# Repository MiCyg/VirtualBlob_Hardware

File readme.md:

# Virtual Blob Hardware

[← Back to main repository](https://github.com/MiCyg/VirtualBlob.git)

---

The device consists of three PCBs:
- `MainBoard` – microcontroller and peripheral interfaces
- `PowerBoard` – USB connector and battery charging circuit
- `LedBoard` – LED matrix driven by the MAX7219

Components on the boards:
- RP2040 microcontroller with SWD programming interface
- Accelerometer LIS3DH
- Capacitive touch sensor AT42QT1011
- Light sensor (LDR with resistor divider)
- Li-Po battery (LP852040)
- Battery charger MCP73811T

## Description

The `MainBoard` and `PowerBoard` are connected using a custom-designed `EdgeConn` board-to-board connector, allowing a 90° connection between the two.
Due to the small overall size and the position of the USB connector, I decided to use a ready-made LED matrix module. This approach saves valuable PCB space on the `MainBoard`, which is limited by the placement of the edge connector.

The device is designed to operate continuously from a Li-Po battery. Therefore, proper power management in sleep mode is crucial. To reduce power consumption, a high-side P-MOSFET switch is used to disconnect the accelerometer and light sensors when the system enters sleep mode. The capacitive touch sensor remains powered at all times, as it is responsible for waking up the device.

## Assembled Boards

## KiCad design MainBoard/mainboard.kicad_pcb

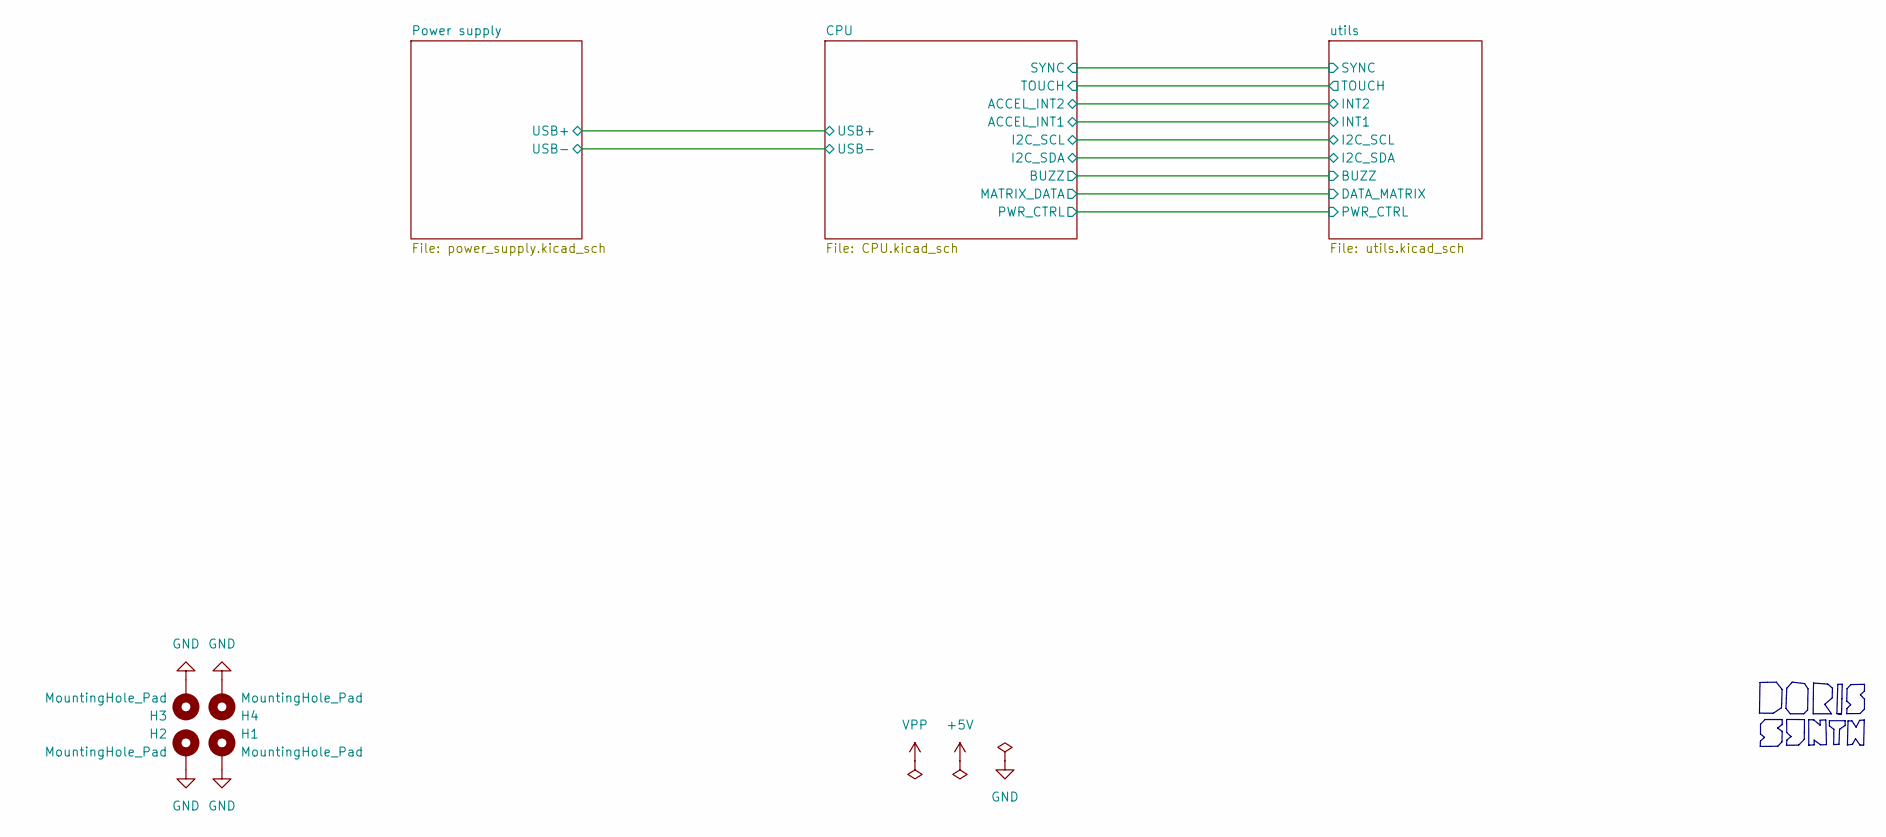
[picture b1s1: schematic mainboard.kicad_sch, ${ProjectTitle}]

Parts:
H1, H2, H3, H4: MountingHole_Pad; MountingHole_2.5mm

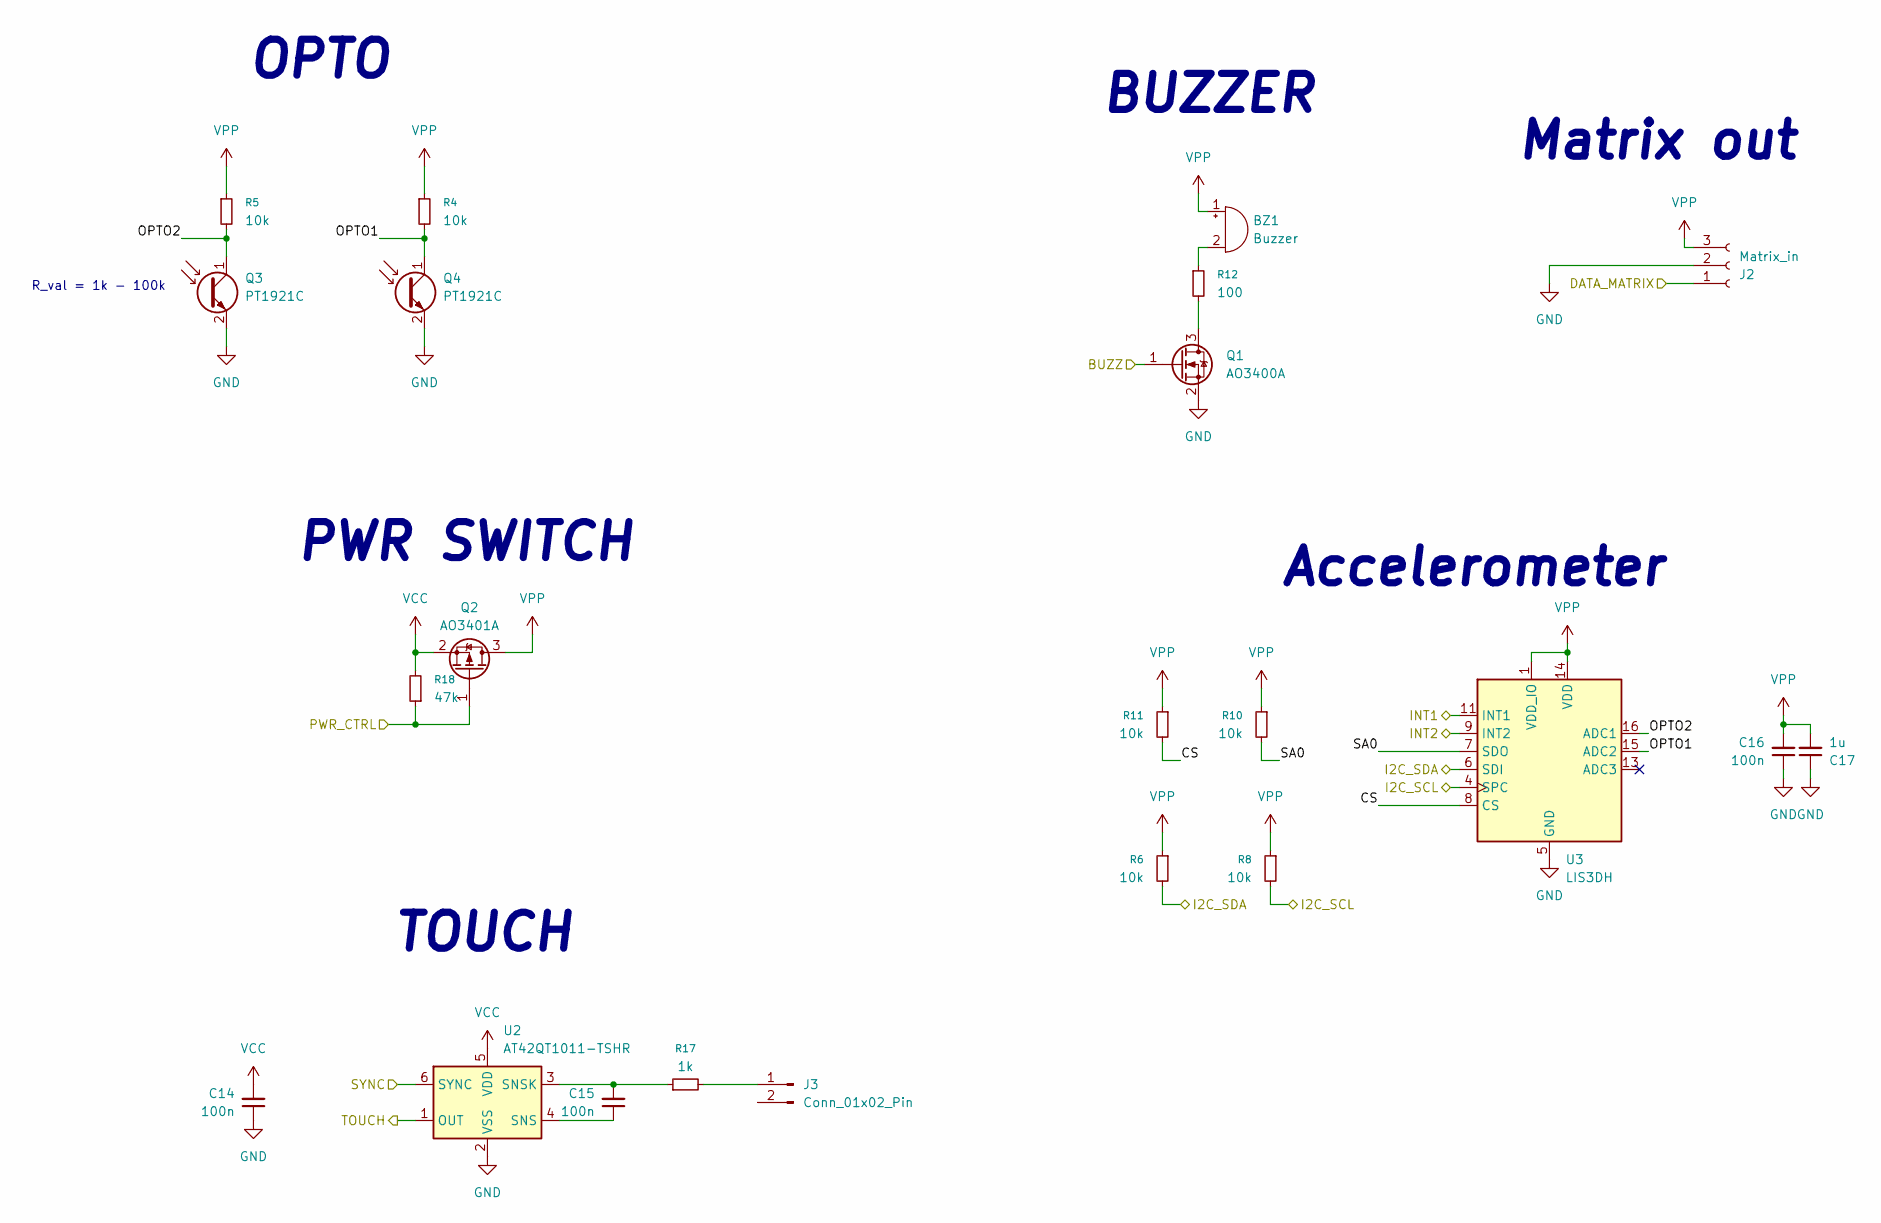
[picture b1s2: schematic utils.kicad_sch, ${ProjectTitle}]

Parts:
BZ1: Buzzer; Buzzer_SMD_5020
C14, C15, C16: 100n; C_0603_1608Metric_Pad1.08x0.95mm_HandSolder
C17: 1u; C_0603_1608Metric_Pad1.08x0.95mm_HandSolder
J2: Matrix_in; JST_PH_B3B-PH-K_1x03_P2.00mm_Vertical
J3: Conn_01x02_Pin; FW-UU_04_08_15
Q1: AO3400A; SOT-23
Q2: AO3401A; SOT-23
Q3, Q4: PT1921C; D_0603_1608Metric_Pad1.05x0.95mm_HandSolder
R4, R5, R6, R8, R10, R11: 10k; R_0603_1608Metric_Pad0.98x0.95mm_HandSolder
R12: 100; R_0603_1608Metric_Pad0.98x0.95mm_HandSolder
R17: 1k; R_0603_1608Metric_Pad0.98x0.95mm_HandSolder
R18: 47k; R_0603_1608Metric_Pad0.98x0.95mm_HandSolder
U2: AT42QT1011-TSHR; SOT-23-6
U3: LIS3DH; LGA-16_3x3mm_P0.5mm_LayoutBorder3x5y

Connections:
/CPU/ACCEL_INT1: U3.11 (INT1); also elsewhere on the board
/CPU/ACCEL_INT2: U3.9 (INT2); also elsewhere on the board
/CPU/BUZZ: Q1.1 (G); also elsewhere on the board
/CPU/I2C_SCL: R8.2, U3.4 (SPC); also elsewhere on the board
/CPU/I2C_SDA: R6.2, U3.6 (SDI); also elsewhere on the board
/CPU/MATRIX_DATA: J2.1; also elsewhere on the board
/CPU/PWR_CTRL: Q2.1 (G), R18.1; also elsewhere on the board
/CPU/SYNC: U2.6 (SYNC); also elsewhere on the board
/CPU/TOUCH: U2.1 (OUT); also elsewhere on the board
/utils/CS: R11.2, U3.8 (CS)
/utils/OPTO1: Q4.1 (C), R4.2, U3.15 (ADC2)
/utils/OPTO2: Q3.1 (C), R5.2, U3.16 (ADC1)
/utils/SA0: R10.2, U3.7 (SDO)
GND: C14.1, C16.1, C17.1, J2.2, Q1.2 (S), Q3.2 (E), Q4.2 (E), U2.2 (VSS), U3.5 (GND), U3.10 (GND), U3.12 (GND); also elsewhere on the board
unnamed: BZ1.2 (-), R12.1
unnamed: J3.1, R17.2
unnamed: Q1.3 (D), R12.2
unnamed: C15.1, U2.4 (SNS)
unnamed: C15.2, R17.1, U2.3 (SNSK)
VCC: C14.2, Q2.2 (S), R18.2, U2.5 (VDD); also elsewhere on the board
VPP: BZ1.1 (+), C16.2, C17.2, J2.3, Q2.3 (D), R4.1, R5.1, R6.1, R8.1, R10.1, R11.1, U3.1 (VDD_IO), U3.14 (VDD)

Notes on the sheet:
OPTO
R_val = 1k - 100k
Matrix out
PWR SWITCH
BUZZER
TOUCH
Accelerometer

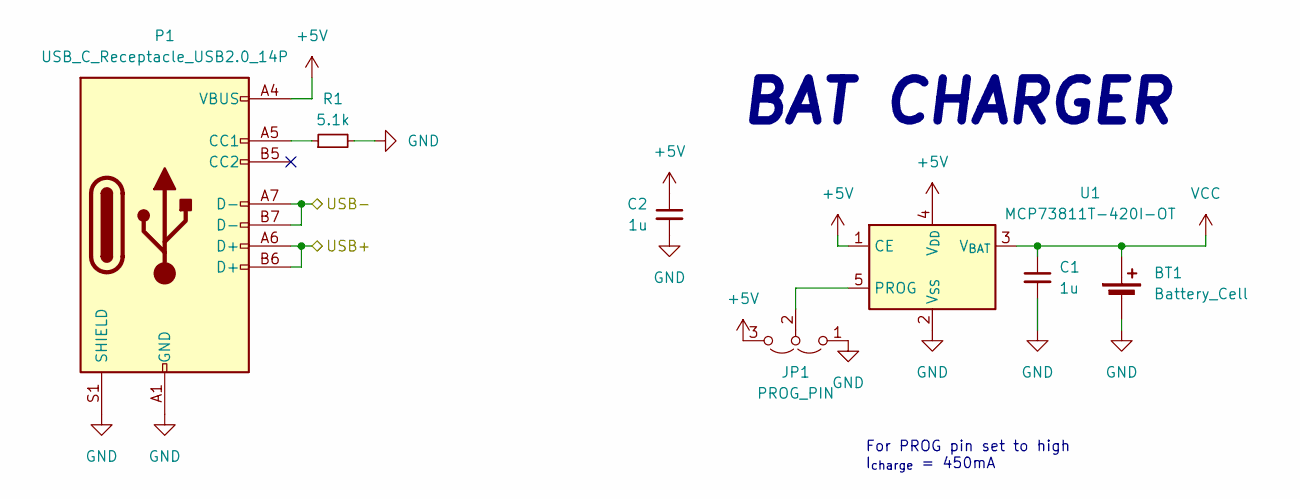
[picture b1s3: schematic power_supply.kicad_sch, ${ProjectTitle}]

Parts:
BT1: Battery_Cell; Molex_PicoBlade_53047-0210_1x02_P1.25mm_Vertical
C1, C2: 1u; C_0603_1608Metric_Pad1.08x0.95mm_HandSolder
JP1: PROG_PIN; SolderJumper-3_P1.3mm_Open_RoundedPad1.0x1.5mm
P1: USB_C_Receptacle_USB2.0_14P; USB_C_Receptacle_G-Switch_GT-USB-7010ASV
R1: 5.1k; R_0603_1608Metric_Pad0.98x0.95mm_HandSolder
U1: MCP73811T-420I-OT; SOT-23-5

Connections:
+5V: C2.1, JP1.3 (B), P1.A4 (VBUS), P1.A9 (VBUS), P1.B4 (VBUS), P1.B9 (VBUS), U1.1 (CE), U1.4 (V_{DD})
/CPU/USB+: P1.A6 (D+), P1.B6 (D+); also elsewhere on the board
/CPU/USB-: P1.A7 (D-), P1.B7 (D-); also elsewhere on the board
GND: BT1.2 (-), C1.2, C2.2, JP1.1 (A), P1.A1 (GND), P1.A12 (GND), P1.B1 (GND), P1.B12 (GND), P1.S1 (SHIELD), R1.2, U1.2 (V_{SS}); also elsewhere on the board
unnamed: JP1.2 (C), U1.5 (PROG)
unnamed: P1.A5 (CC1), R1.1
VCC: BT1.1 (+), C1.1, U1.3 (V_{BAT}); also elsewhere on the board

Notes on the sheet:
BAT CHARGER
For PROG pin set to high I_{charge} = 450mA

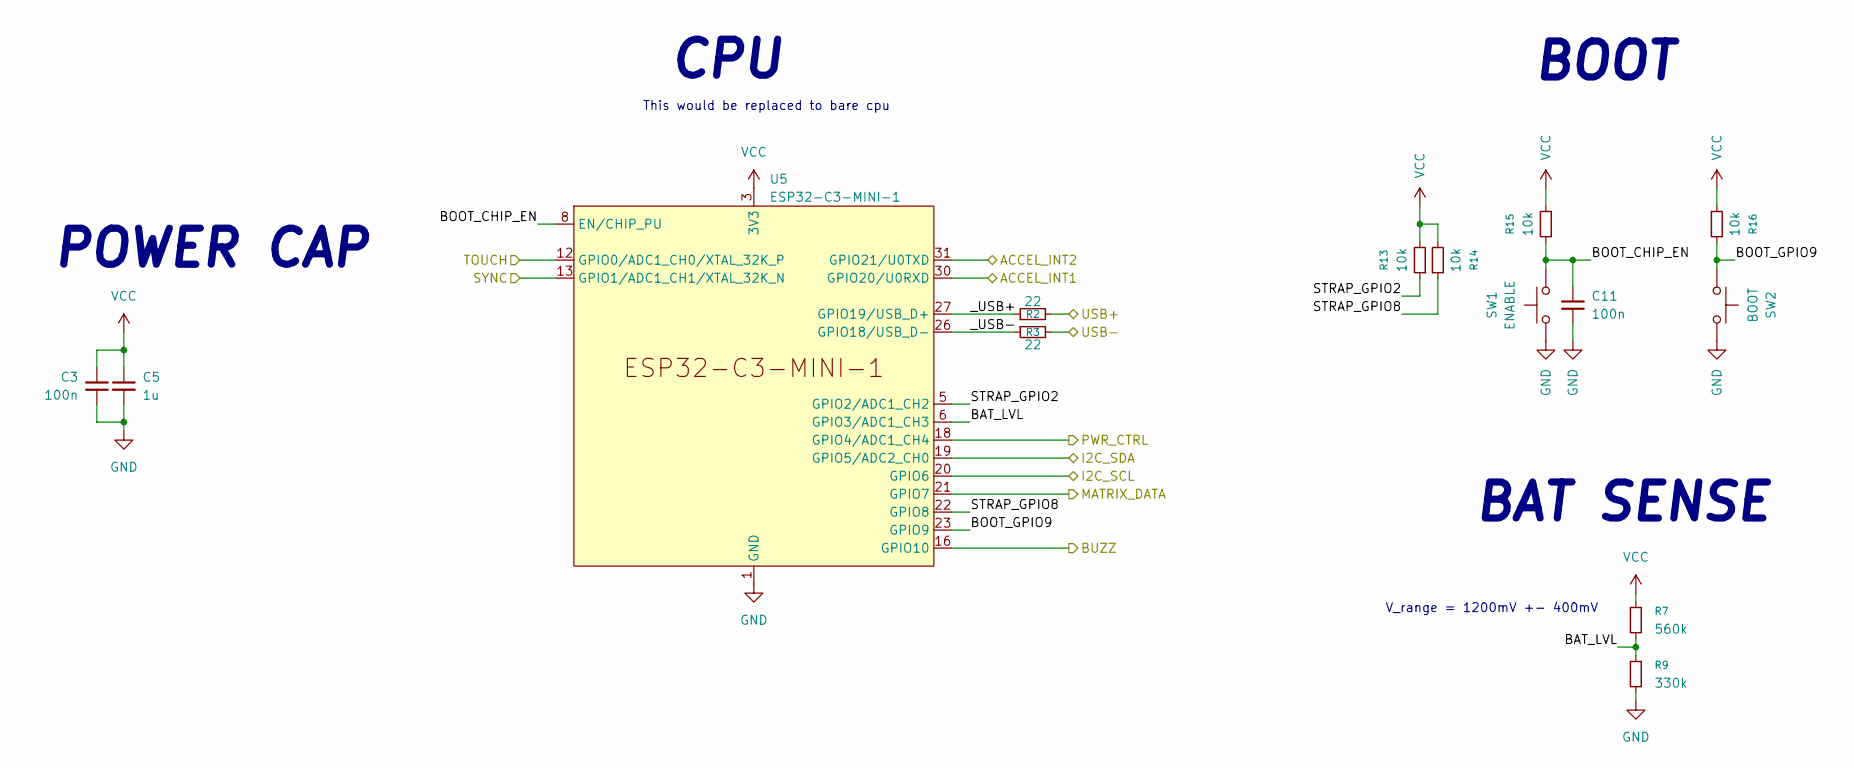
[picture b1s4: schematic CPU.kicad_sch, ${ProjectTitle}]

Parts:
C3, C11: 100n; C_0603_1608Metric_Pad1.08x0.95mm_HandSolder
C5: 1u; C_0603_1608Metric_Pad1.08x0.95mm_HandSolder
R2, R3: 22; R_0603_1608Metric_Pad0.98x0.95mm_HandSolder
R7: 560k; R_0603_1608Metric_Pad0.98x0.95mm_HandSolder
R9: 330k; R_0603_1608Metric_Pad0.98x0.95mm_HandSolder
R13, R14, R15, R16: 10k; R_0603_1608Metric_Pad0.98x0.95mm_HandSolder
SW1: ENABLE; SW_SPST_CK_RS282G05A3
SW2: BOOT; SW_SPST_CK_RS282G05A3
U5: ESP32-C3-MINI-1

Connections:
/CPU/ACCEL_INT1: U5.30 (GPIO20/U0RXD); also elsewhere on the board
/CPU/ACCEL_INT2: U5.31 (GPIO21/U0TXD); also elsewhere on the board
/CPU/BAT_LVL: R7.2, R9.1, U5.6 (GPIO3/ADC1_CH3)
/CPU/BOOT_CHIP_EN: C11.2, R15.2, SW1.2, U5.8 (EN/CHIP_PU)
/CPU/BOOT_GPIO9: R16.2, SW2.2, U5.23 (GPIO9)
/CPU/BUZZ: U5.16 (GPIO10); also elsewhere on the board
/CPU/I2C_SCL: U5.20 (GPIO6); also elsewhere on the board
/CPU/I2C_SDA: U5.19 (GPIO5/ADC2_CH0); also elsewhere on the board
/CPU/MATRIX_DATA: U5.21 (GPIO7); also elsewhere on the board
/CPU/PWR_CTRL: U5.18 (GPIO4/ADC1_CH4); also elsewhere on the board
/CPU/STRAP_GPIO2: R13.1, U5.5 (GPIO2/ADC1_CH2)
/CPU/STRAP_GPIO8: R14.1, U5.22 (GPIO8)
/CPU/SYNC: U5.13 (GPIO1/ADC1_CH1/XTAL_32K_N); also elsewhere on the board
/CPU/TOUCH: U5.12 (GPIO0/ADC1_CH0/XTAL_32K_P); also elsewhere on the board
/CPU/USB+: R2.2; also elsewhere on the board
/CPU/USB-: R3.2; also elsewhere on the board
/CPU/_USB+: R2.1, U5.27 (GPIO19/USB_D+)
/CPU/_USB-: R3.1, U5.26 (GPIO18/USB_D-)
GND: C3.1, C5.2, C11.1, R9.2, SW1.1, SW2.1, U5.1 (GND), U5.2 (GND), U5.11 (GND), U5.14 (GND), U5.36 (GND), U5.37 (GND), U5.38 (GND), U5.39 (GND), U5.40 (GND), U5.41 (GND), U5.42 (GND), U5.43 (GND), U5.44 (GND), U5.45 (GND), U5.46 (GND), U5.47 (GND), U5.48 (GND), U5.49 (GND), U5.50 (GND), U5.51 (GND), U5.52 (GND), U5.53 (GND); also elsewhere on the board
VCC: C3.2, C5.1, R7.1, R13.2, R14.2, R15.1, R16.1, U5.3 (3V3); also elsewhere on the board

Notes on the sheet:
CPU
BOOT
This would be replaced to bare cpu
BAT SENSE
POWER CAP
V_range = 1200mV +- 400mV

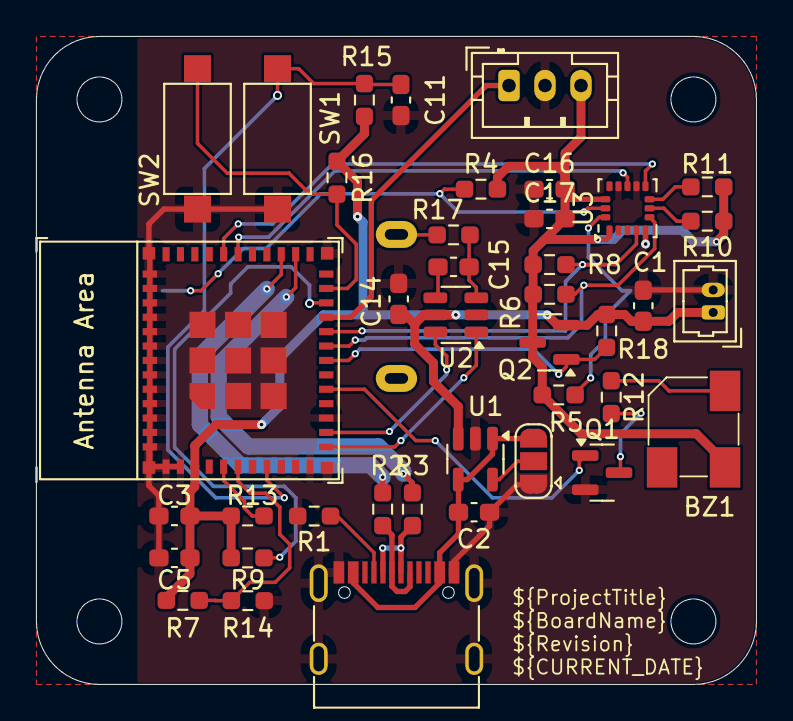
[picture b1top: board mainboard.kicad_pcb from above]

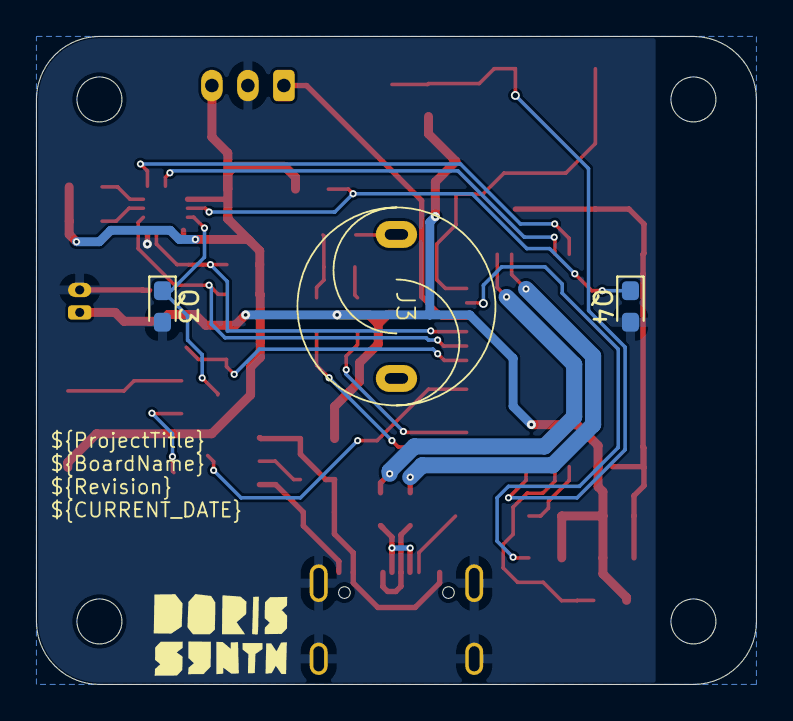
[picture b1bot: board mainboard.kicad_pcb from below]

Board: 2 copper layers, 40.0 x 36.0 mm, 47 parts (3 on the bottom side), 33 nets.

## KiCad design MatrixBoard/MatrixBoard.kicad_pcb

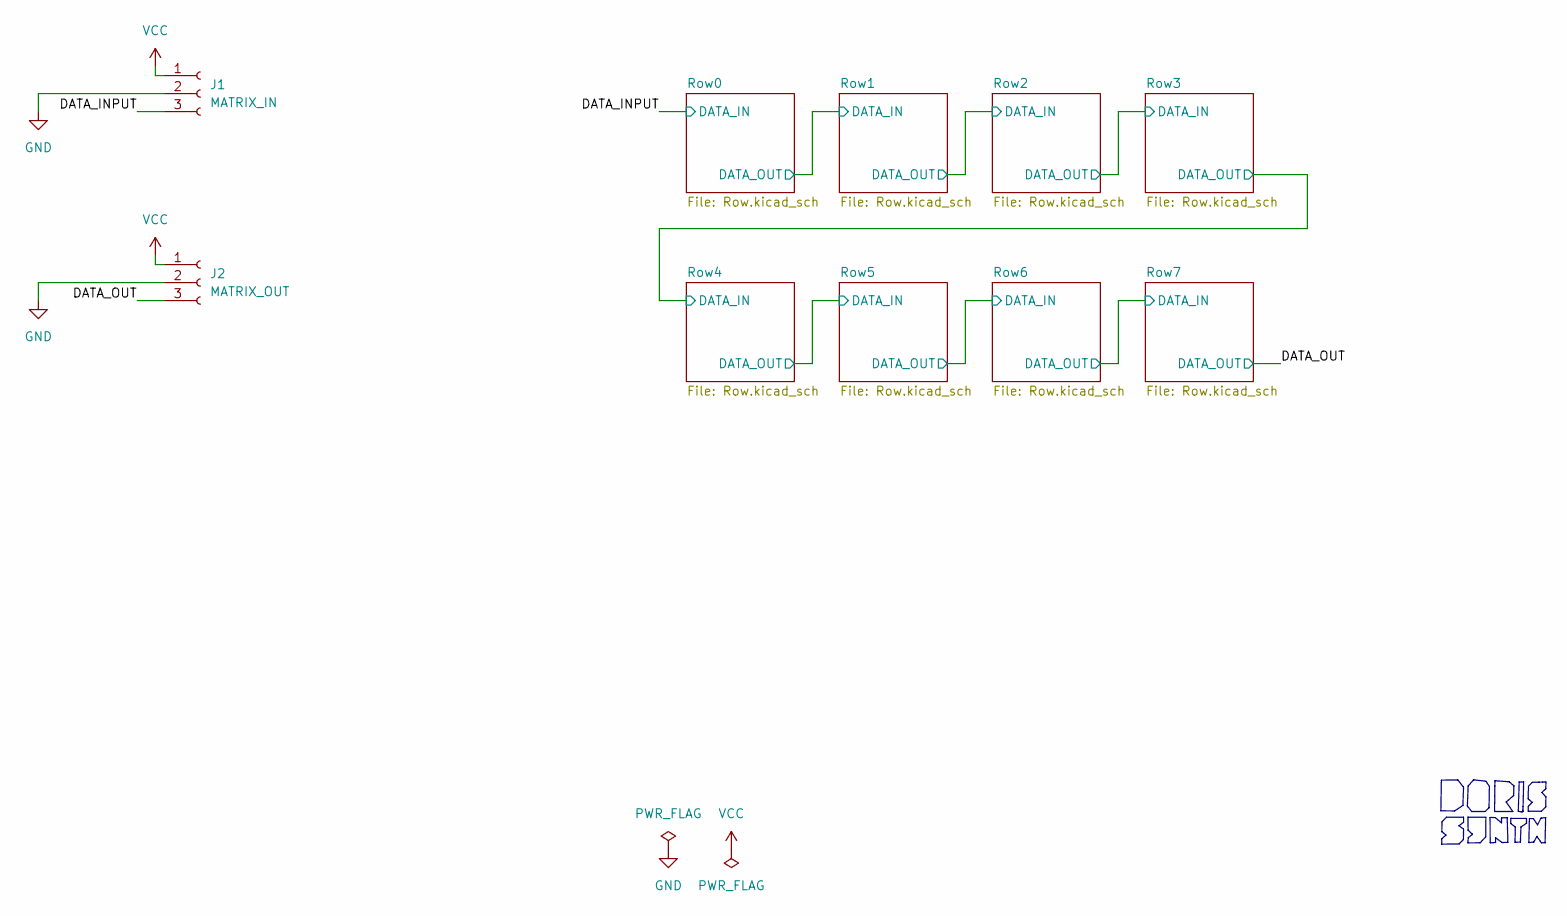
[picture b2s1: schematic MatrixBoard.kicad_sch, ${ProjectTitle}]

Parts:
J1: MATRIX_IN; PinHeader_1x03_P2.54mm_Vertical
J2: MATRIX_OUT; PinHeader_1x03_P2.54mm_Vertical

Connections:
/DATA_INPUT: J1.3; also elsewhere on the board
/DATA_OUT: J2.3; also elsewhere on the board
GND: J1.2, J2.2; also elsewhere on the board
VCC: J1.1, J2.1; also elsewhere on the board

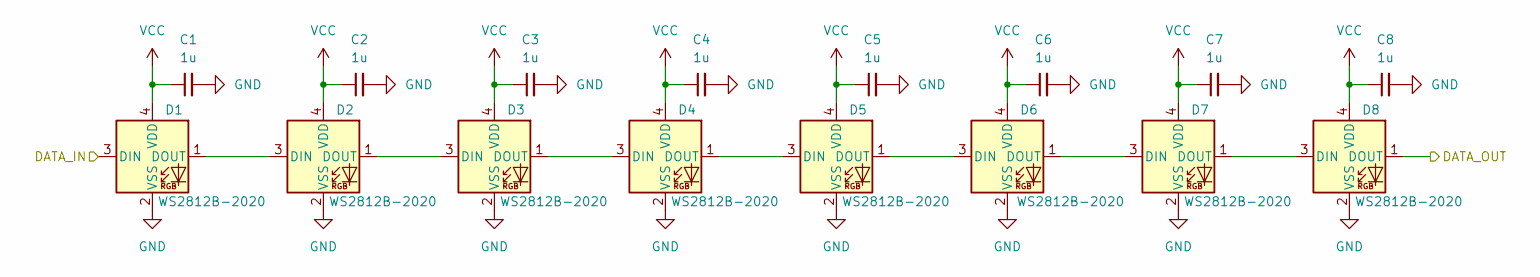
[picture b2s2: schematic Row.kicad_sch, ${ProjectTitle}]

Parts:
C1, C2, C3, C4, C5, C6, C7, C8: 1u; C_0603_1608Metric_Pad1.08x0.95mm_HandSolder
D1, D2, D3, D4, D5, D6, D7, D8: WS2812B-2020; LED_WS2812B-2020_PLCC4_2.0x2.0mm

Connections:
/DATA_INPUT: D1.3 (DIN); also elsewhere on the board
/Row0/DATA_OUT: D8.1 (DOUT); also elsewhere on the board
GND: C1.2, C2.2, C3.2, C4.2, C5.2, C6.2, C7.2, C8.2, D1.2 (VSS), D2.2 (VSS), D3.2 (VSS), D4.2 (VSS), D5.2 (VSS), D6.2 (VSS), D7.2 (VSS), D8.2 (VSS); also elsewhere on the board
unnamed: D1.1 (DOUT), D2.3 (DIN)
unnamed: D2.1 (DOUT), D3.3 (DIN)
unnamed: D3.1 (DOUT), D4.3 (DIN)
unnamed: D4.1 (DOUT), D5.3 (DIN)
unnamed: D5.1 (DOUT), D6.3 (DIN)
unnamed: D6.1 (DOUT), D7.3 (DIN)
unnamed: D7.1 (DOUT), D8.3 (DIN)
VCC: C1.1, C2.1, C3.1, C4.1, C5.1, C6.1, C7.1, C8.1, D1.4 (VDD), D2.4 (VDD), D3.4 (VDD), D4.4 (VDD), D5.4 (VDD), D6.4 (VDD), D7.4 (VDD), D8.4 (VDD); also elsewhere on the board

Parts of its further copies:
C9, C10, C11, C12, C13, C14, C15, C16, C17, C18, C19, C20, C21, C22, C23, C24, C25, C26, C27, C28, C29, C30, C31, C32, C33, C34, C35, C36, C37, C38, C39, C40, C41, C42, C43, C44, C45, C46, C47, C48, C49, C50, C51, C52, C53, C54, C55, C56, C57, C58, C59, C60, C61, C62, C63, C64: 1u; C_0603_1608Metric_Pad1.08x0.95mm_HandSolder
D9, D10, D11, D12, D13, D14, D15, D16, D17, D18, D19, D20, D21, D22, D23, D24, D25, D26, D27, D28, D29, D30, D31, D32, D33, D34, D35, D36, D37, D38, D39, D40, D41, D42, D43, D44, D45, D46, D47, D48, D49, D50, D51, D52, D53, D54, D55, D56, D57, D58, D59, D60, D61, D62, D63, D64: WS2812B-2020; LED_WS2812B-2020_PLCC4_2.0x2.0mm

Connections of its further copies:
/DATA_OUT: D64.1 (DOUT); also elsewhere on the board
/Row0/DATA_OUT: D9.3 (DIN); also elsewhere on the board
/Row1/DATA_OUT: D16.1 (DOUT), D17.3 (DIN)
/Row2/DATA_OUT: D24.1 (DOUT), D25.3 (DIN)
/Row3/DATA_OUT: D32.1 (DOUT), D33.3 (DIN)
/Row4/DATA_OUT: D40.1 (DOUT), D41.3 (DIN)
/Row5/DATA_OUT: D48.1 (DOUT), D49.3 (DIN)
/Row6/DATA_OUT: D56.1 (DOUT), D57.3 (DIN)
GND: C9.2, C10.2, C11.2, C12.2, C13.2, C14.2, C15.2, C16.2, C17.2, C18.2, C19.2, C20.2, C21.2, C22.2, C23.2, C24.2, C25.2, C26.2, C27.2, C28.2, C29.2, C30.2, C31.2, C32.2, C33.2, C34.2, C35.2, C36.2, C37.2, C38.2, C39.2, C40.2, C41.2, C42.2, C43.2, C44.2, C45.2, C46.2, C47.2, C48.2, C49.2, C50.2, C51.2, C52.2, C53.2, C54.2, C55.2, C56.2, C57.2, C58.2, C59.2, C60.2, C61.2, C62.2, C63.2, C64.2, D9.2 (VSS), D10.2 (VSS), D11.2 (VSS), D12.2 (VSS), D13.2 (VSS), D14.2 (VSS), D15.2 (VSS), D16.2 (VSS), D17.2 (VSS), D18.2 (VSS), D19.2 (VSS), D20.2 (VSS), D21.2 (VSS), D22.2 (VSS), D23.2 (VSS), D24.2 (VSS), D25.2 (VSS), D26.2 (VSS), D27.2 (VSS), D28.2 (VSS), D29.2 (VSS), D30.2 (VSS), D31.2 (VSS), D32.2 (VSS), D33.2 (VSS), D34.2 (VSS), D35.2 (VSS), D36.2 (VSS), D37.2 (VSS), D38.2 (VSS), D39.2 (VSS), D40.2 (VSS), D41.2 (VSS), D42.2 (VSS), D43.2 (VSS), D44.2 (VSS), D45.2 (VSS), D46.2 (VSS), D47.2 (VSS), D48.2 (VSS), D49.2 (VSS), D50.2 (VSS), D51.2 (VSS), D52.2 (VSS), D53.2 (VSS), D54.2 (VSS), D55.2 (VSS), D56.2 (VSS), D57.2 (VSS), D58.2 (VSS), D59.2 (VSS), D60.2 (VSS), D61.2 (VSS), D62.2 (VSS), D63.2 (VSS), D64.2 (VSS); also elsewhere on the board
unnamed: D9.1 (DOUT), D10.3 (DIN)
unnamed: D10.1 (DOUT), D11.3 (DIN)
unnamed: D11.1 (DOUT), D12.3 (DIN)
unnamed: D12.1 (DOUT), D13.3 (DIN)
unnamed: D13.1 (DOUT), D14.3 (DIN)
unnamed: D14.1 (DOUT), D15.3 (DIN)
unnamed: D15.1 (DOUT), D16.3 (DIN)
unnamed: D17.1 (DOUT), D18.3 (DIN)
unnamed: D18.1 (DOUT), D19.3 (DIN)
unnamed: D19.1 (DOUT), D20.3 (DIN)
unnamed: D20.1 (DOUT), D21.3 (DIN)
unnamed: D21.1 (DOUT), D22.3 (DIN)
unnamed: D22.1 (DOUT), D23.3 (DIN)
unnamed: D23.1 (DOUT), D24.3 (DIN)
unnamed: D25.1 (DOUT), D26.3 (DIN)
unnamed: D26.1 (DOUT), D27.3 (DIN)
unnamed: D27.1 (DOUT), D28.3 (DIN)
unnamed: D28.1 (DOUT), D29.3 (DIN)
unnamed: D29.1 (DOUT), D30.3 (DIN)
unnamed: D30.1 (DOUT), D31.3 (DIN)
unnamed: D31.1 (DOUT), D32.3 (DIN)
unnamed: D33.1 (DOUT), D34.3 (DIN)
unnamed: D34.1 (DOUT), D35.3 (DIN)
unnamed: D35.1 (DOUT), D36.3 (DIN)
unnamed: D36.1 (DOUT), D37.3 (DIN)
unnamed: D37.1 (DOUT), D38.3 (DIN)
unnamed: D38.1 (DOUT), D39.3 (DIN)
unnamed: D39.1 (DOUT), D40.3 (DIN)
unnamed: D41.1 (DOUT), D42.3 (DIN)
unnamed: D42.1 (DOUT), D43.3 (DIN)
unnamed: D43.1 (DOUT), D44.3 (DIN)
unnamed: D44.1 (DOUT), D45.3 (DIN)
unnamed: D45.1 (DOUT), D46.3 (DIN)
unnamed: D46.1 (DOUT), D47.3 (DIN)
unnamed: D47.1 (DOUT), D48.3 (DIN)
unnamed: D49.1 (DOUT), D50.3 (DIN)
unnamed: D50.1 (DOUT), D51.3 (DIN)
unnamed: D51.1 (DOUT), D52.3 (DIN)
unnamed: D52.1 (DOUT), D53.3 (DIN)
unnamed: D53.1 (DOUT), D54.3 (DIN)
unnamed: D54.1 (DOUT), D55.3 (DIN)
unnamed: D55.1 (DOUT), D56.3 (DIN)
unnamed: D57.1 (DOUT), D58.3 (DIN)
unnamed: D58.1 (DOUT), D59.3 (DIN)
unnamed: D59.1 (DOUT), D60.3 (DIN)
unnamed: D60.1 (DOUT), D61.3 (DIN)
unnamed: D61.1 (DOUT), D62.3 (DIN)
unnamed: D62.1 (DOUT), D63.3 (DIN)
unnamed: D63.1 (DOUT), D64.3 (DIN)
VCC: C9.1, C10.1, C11.1, C12.1, C13.1, C14.1, C15.1, C16.1, C17.1, C18.1, C19.1, C20.1, C21.1, C22.1, C23.1, C24.1, C25.1, C26.1, C27.1, C28.1, C29.1, C30.1, C31.1, C32.1, C33.1, C34.1, C35.1, C36.1, C37.1, C38.1, C39.1, C40.1, C41.1, C42.1, C43.1, C44.1, C45.1, C46.1, C47.1, C48.1, C49.1, C50.1, C51.1, C52.1, C53.1, C54.1, C55.1, C56.1, C57.1, C58.1, C59.1, C60.1, C61.1, C62.1, C63.1, C64.1, D9.4 (VDD), D10.4 (VDD), D11.4 (VDD), D12.4 (VDD), D13.4 (VDD), D14.4 (VDD), D15.4 (VDD), D16.4 (VDD), D17.4 (VDD), D18.4 (VDD), D19.4 (VDD), D20.4 (VDD), D21.4 (VDD), D22.4 (VDD), D23.4 (VDD), D24.4 (VDD), D25.4 (VDD), D26.4 (VDD), D27.4 (VDD), D28.4 (VDD), D29.4 (VDD), D30.4 (VDD), D31.4 (VDD), D32.4 (VDD), D33.4 (VDD), D34.4 (VDD), D35.4 (VDD), D36.4 (VDD), D37.4 (VDD), D38.4 (VDD), D39.4 (VDD), D40.4 (VDD), D41.4 (VDD), D42.4 (VDD), D43.4 (VDD), D44.4 (VDD), D45.4 (VDD), D46.4 (VDD), D47.4 (VDD), D48.4 (VDD), D49.4 (VDD), D50.4 (VDD), D51.4 (VDD), D52.4 (VDD), D53.4 (VDD), D54.4 (VDD), D55.4 (VDD), D56.4 (VDD), D57.4 (VDD), D58.4 (VDD), D59.4 (VDD), D60.4 (VDD), D61.4 (VDD), D62.4 (VDD), D63.4 (VDD), D64.4 (VDD); also elsewhere on the board

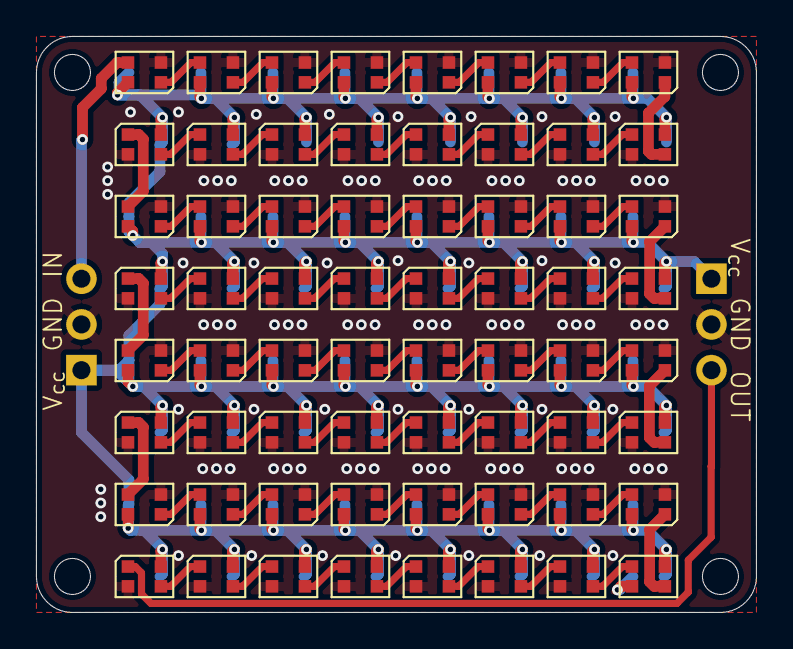
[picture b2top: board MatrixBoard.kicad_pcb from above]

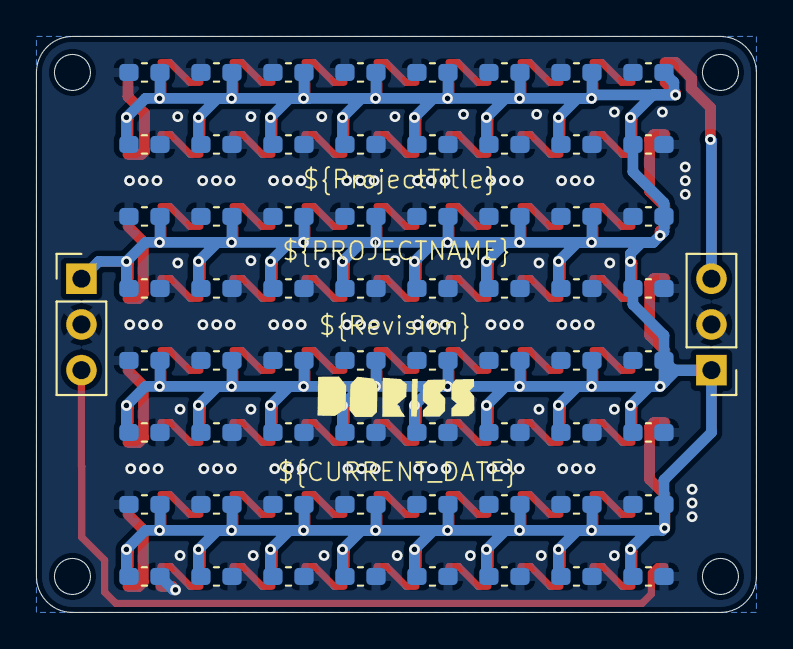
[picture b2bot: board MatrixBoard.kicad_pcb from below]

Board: 2 copper layers, 40.0 x 32.0 mm, 130 parts (66 on the bottom side), 67 nets.

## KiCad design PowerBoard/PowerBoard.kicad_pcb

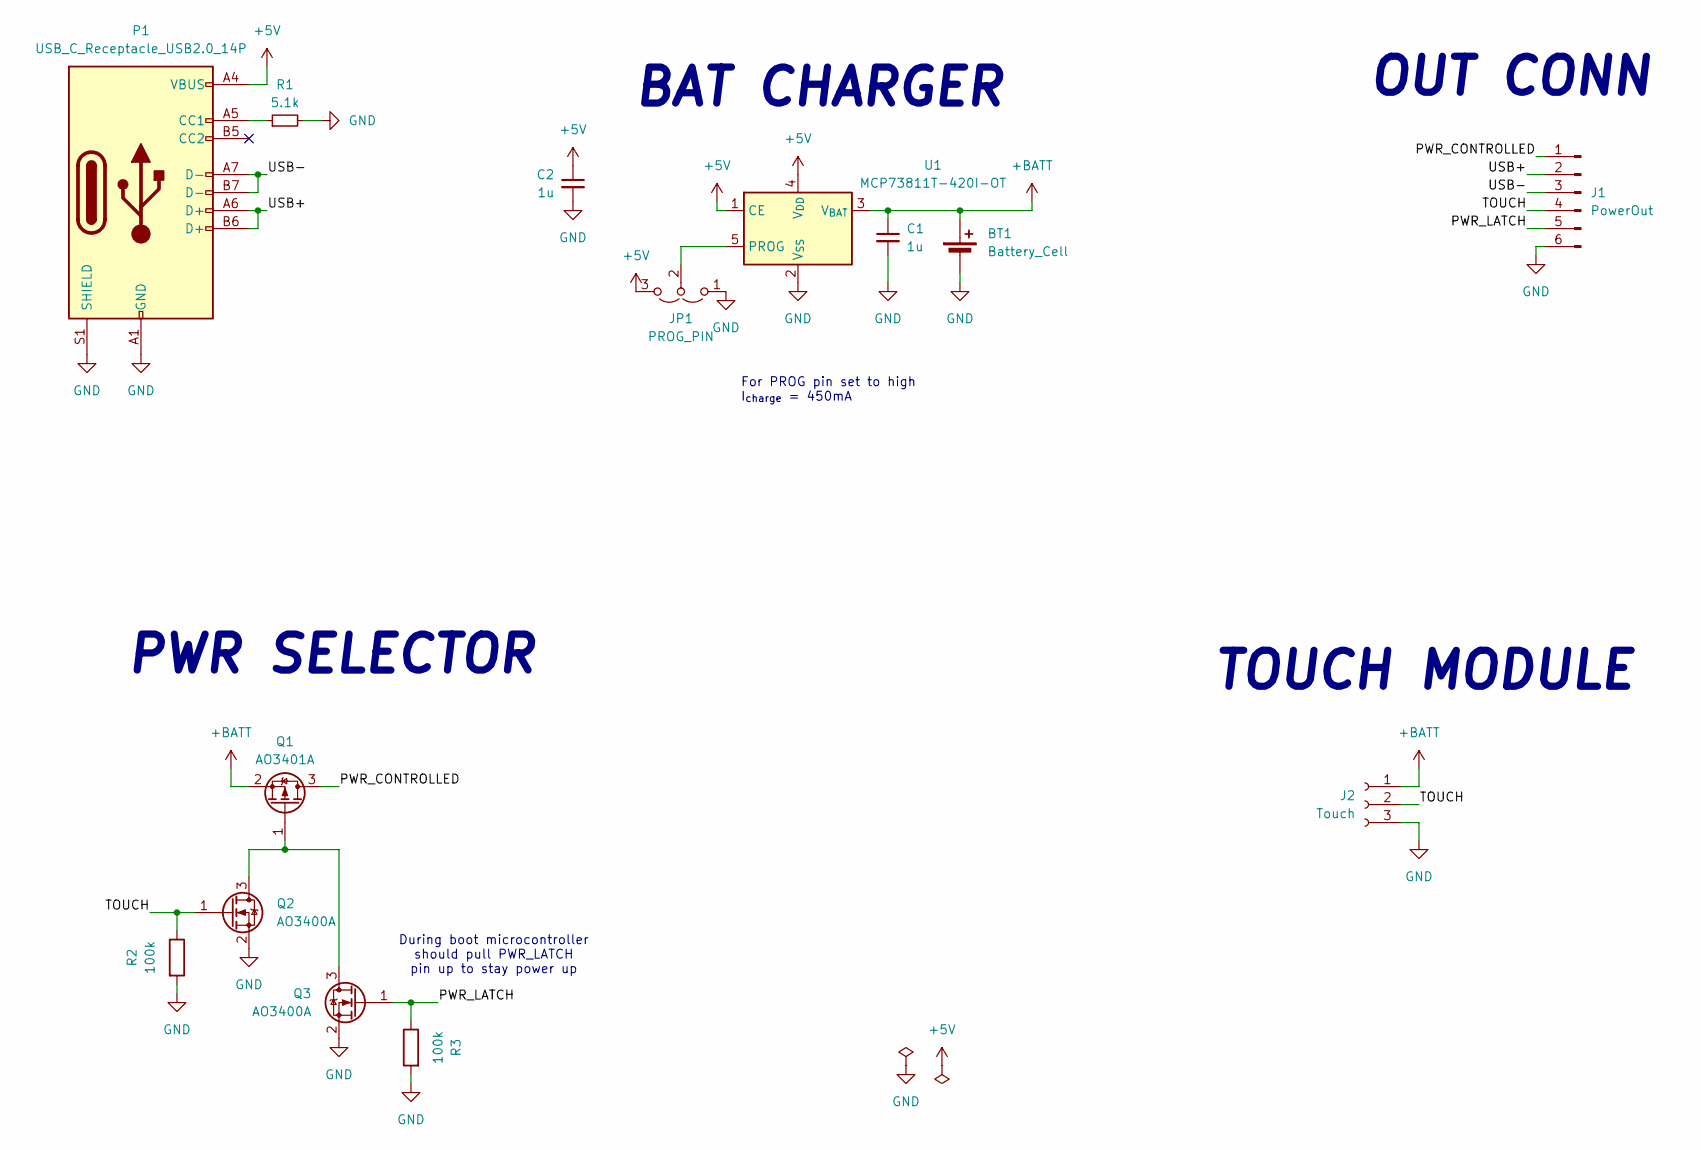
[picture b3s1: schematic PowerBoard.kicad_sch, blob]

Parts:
BT1: Battery_Cell; Molex_PicoBlade_53047-0210_1x02_P1.25mm_Vertical
C1, C2: 1u; C_0603_1608Metric_Pad1.08x0.95mm_HandSolder
J1: PowerOut; edge_conn_03x02_1_6x10mm_pin
J2: Touch; Molex_PicoBlade_53047-0310_1x03_P1.25mm_Vertical
JP1: PROG_PIN; SolderJumper-3_P1.3mm_Open_RoundedPad1.0x1.5mm
P1: USB_C_Receptacle_USB2.0_14P; USB_C_Receptacle_G-Switch_GT-USB-7010ASV
Q1: AO3401A; SOT-23
Q2, Q3: AO3400A; SOT-23
R1: 5.1k; R_0603_1608Metric_Pad0.98x0.95mm_HandSolder
R2, R3: 100k; R_0603_1608Metric_Pad0.98x0.95mm_HandSolder
U1: MCP73811T-420I-OT; SOT-23-5

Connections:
+5V: C2.1, JP1.3 (B), P1.A4 (VBUS), P1.A9 (VBUS), P1.B4 (VBUS), P1.B9 (VBUS), U1.1 (CE), U1.4 (V_{DD})
+BATT: BT1.1 (+), C1.1, J2.1, Q1.2 (S), U1.3 (V_{BAT})
/PWR_CONTROLLED: J1.1, Q1.3 (D)
/PWR_LATCH: J1.5, Q3.1 (G), R3.1
/TOUCH: J1.4, J2.2, Q2.1 (G), R2.1
/USB+: J1.2, P1.A6 (D+), P1.B6 (D+)
/USB-: J1.3, P1.A7 (D-), P1.B7 (D-)
GND: BT1.2 (-), C1.2, C2.2, J1.6, J2.3, JP1.1 (A), P1.A1 (GND), P1.A12 (GND), P1.B1 (GND), P1.B12 (GND), P1.S1 (SHIELD), Q2.2 (S), Q3.2 (S), R1.2, R2.2, R3.2, U1.2 (V_{SS})
unnamed: JP1.2 (C), U1.5 (PROG)
unnamed: P1.A5 (CC1), R1.1
unnamed: Q1.1 (G), Q2.3 (D), Q3.3 (D)

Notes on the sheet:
For PROG pin set to high I_{charge} = 450mA
PWR SELECTOR
OUT CONN
BAT CHARGER
During boot microcontroller should pull PWR_LATCH pin up to stay power up
TOUCH MODULE

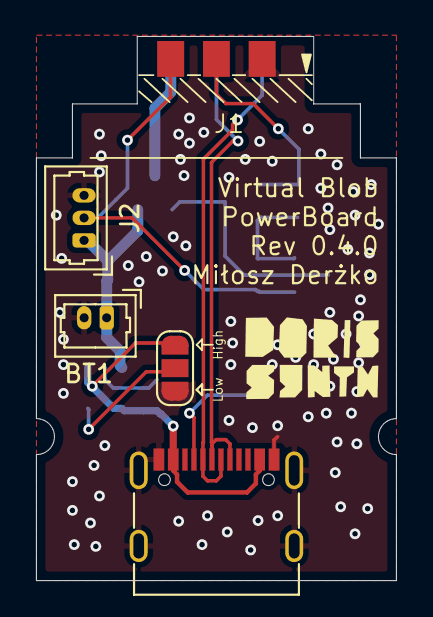
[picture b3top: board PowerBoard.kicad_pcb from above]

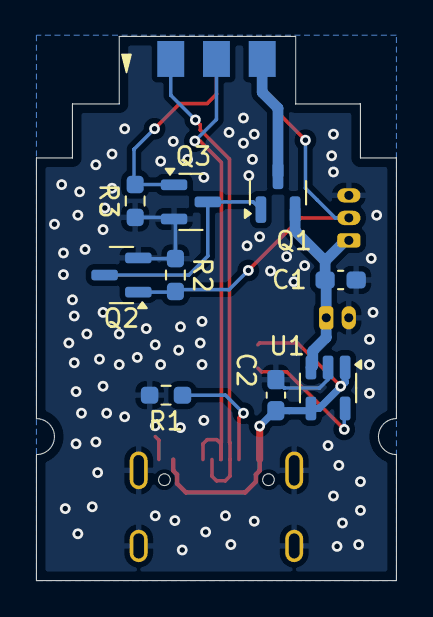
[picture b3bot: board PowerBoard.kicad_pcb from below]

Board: 2 copper layers, 20.0 x 30.2 mm, 14 parts (9 on the bottom side), 11 nets.

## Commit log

2025-10-03 chore: Initial commit
2025-10-18 change revision
2025-10-18 change schematic, use touch controller to enable second bard power. microcontroller should set pin up to latch power
2025-10-19 prepare matrix board
2025-10-19 Change location of tuch sensor, touch button now power up all components, change length. Add buzzer to mainboard and remove touch from them. change revision version
2025-10-19 add buzer, update layout to schematic, make pcb mounting
2025-10-19 update images on readme
2025-11-11 add matrix board, change pico to esp32 microcontroller
2025-11-11 add submodule
2025-11-11 some changes for esp32 board
2025-11-11 change schematic
2025-11-22 Change project assumptions, create new board with esp32-c3
2025-11-22 Udpate project variables and add texts
2025-11-22 Change naming of project
2025-11-22 rename 3d models
2025-11-22 add new spring touch
2025-11-23 Add logo and update project variables
2025-11-23 clean project, change location of some libraries
2025-11-23 Change some opto signals
